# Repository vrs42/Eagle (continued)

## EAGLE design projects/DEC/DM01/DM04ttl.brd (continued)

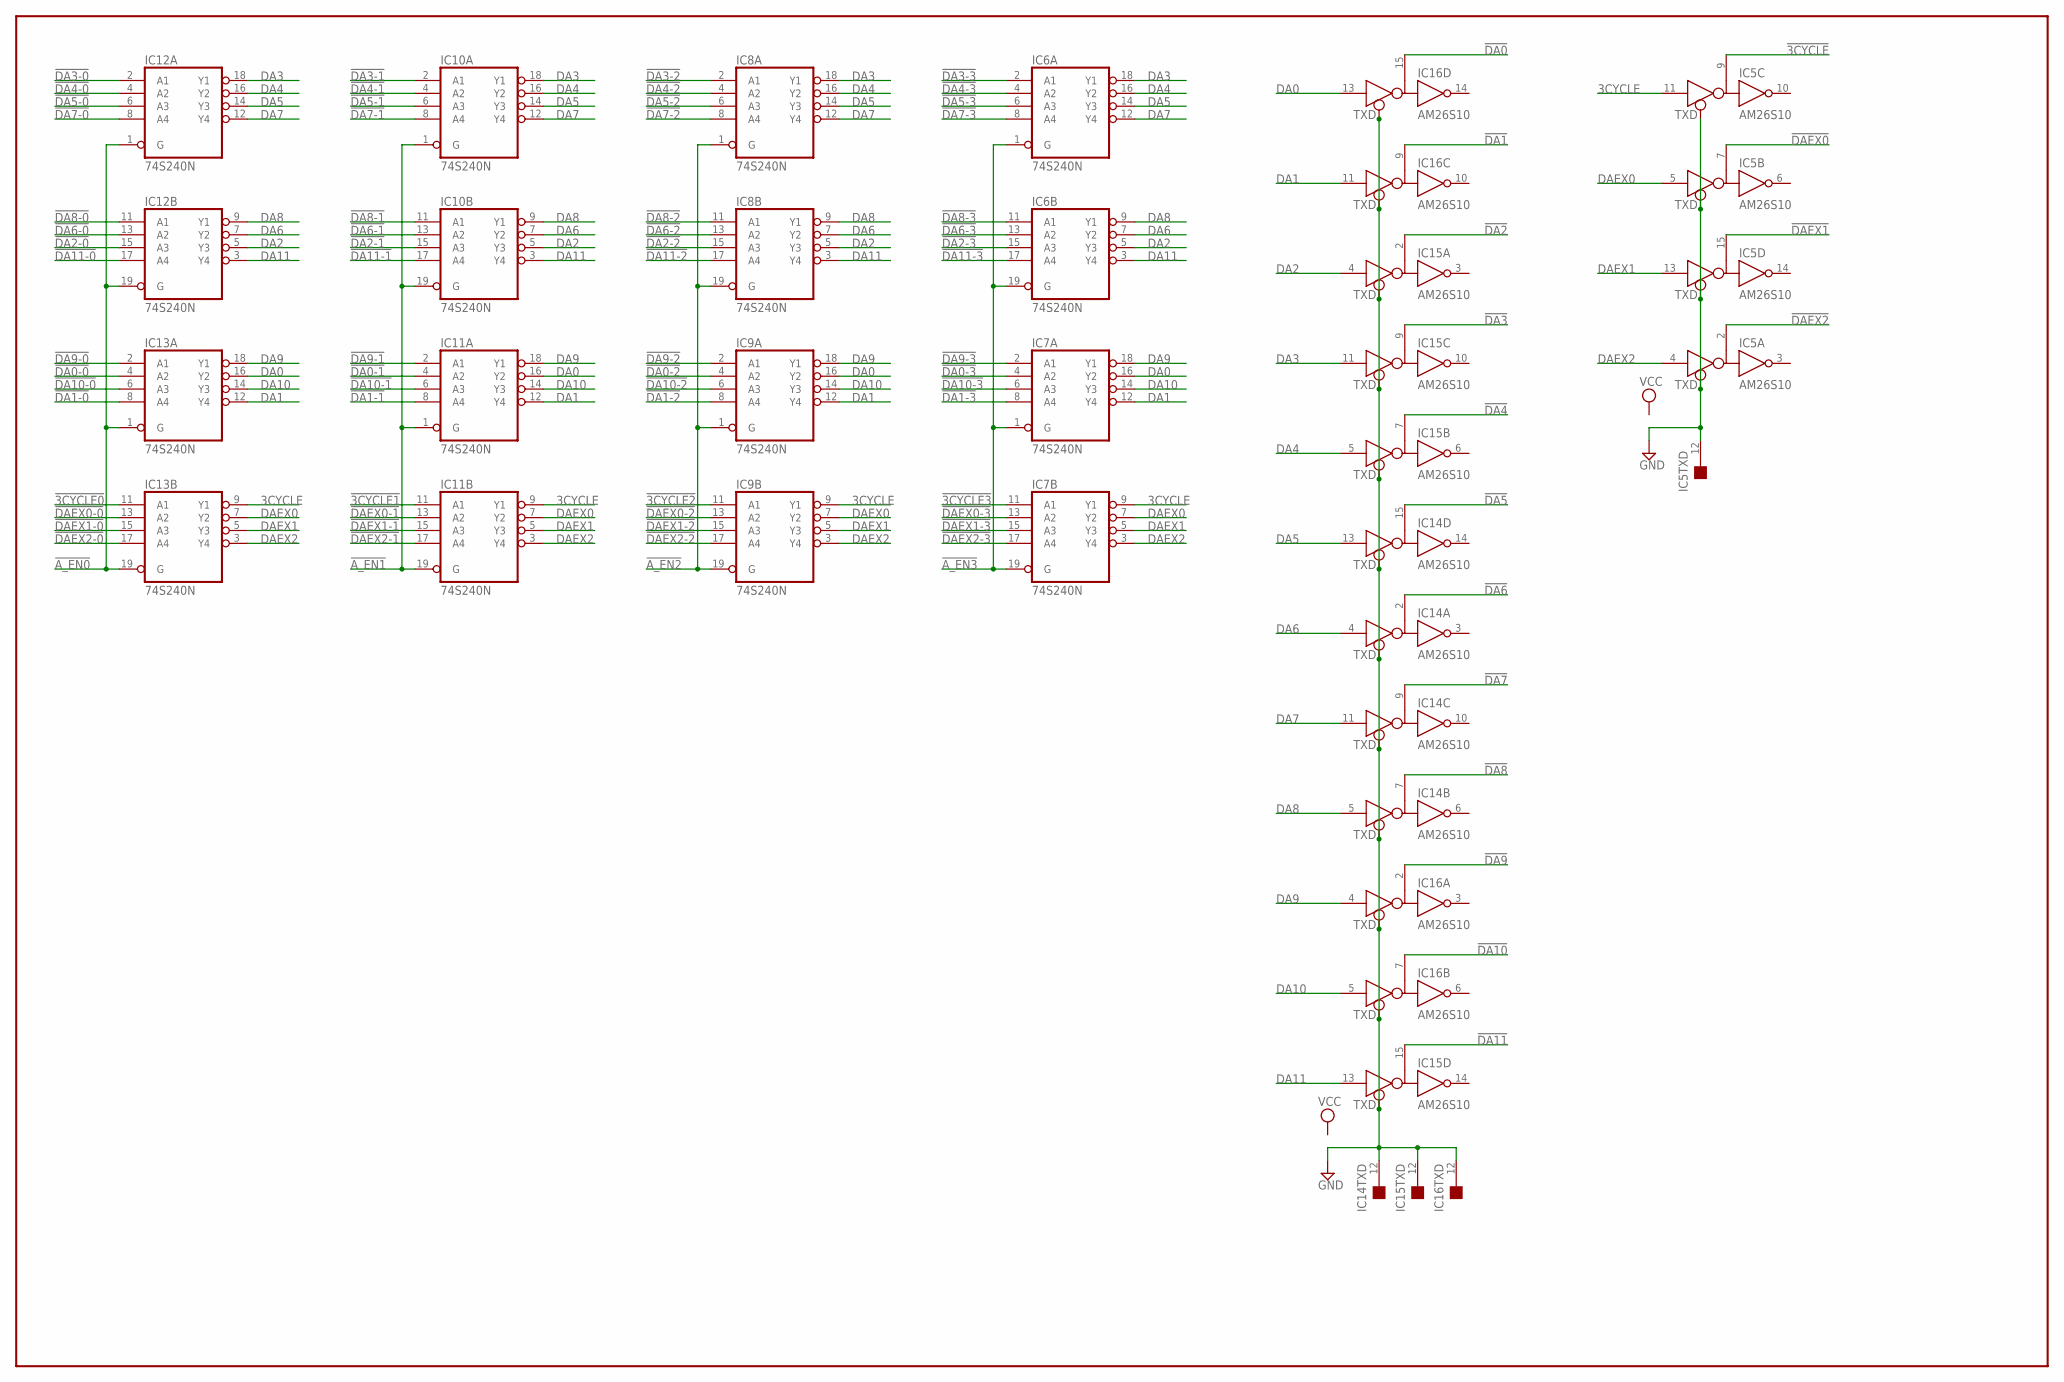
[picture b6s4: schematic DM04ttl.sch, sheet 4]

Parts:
IC5, IC14, IC15, IC16: AM26S10; DIL16
IC6, IC7, IC8, IC9, IC10, IC11, IC12, IC13: 74S240N; DIL20

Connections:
3CYCLE: IC5.11 (D), IC7.9 (Y1), IC9.9 (Y1), IC11.9 (Y1), IC13.9 (Y1)
!3CYCLE: IC5.9 (B); also elsewhere on the board
!3CYCLE0: IC13.11 (A1); also elsewhere on the board
!3CYCLE1: IC11.11 (A1); also elsewhere on the board
!3CYCLE2: IC9.11 (A1); also elsewhere on the board
!3CYCLE3: IC7.11 (A1); also elsewhere on the board
!A_EN0: IC12.1 (G), IC12.19 (G), IC13.1 (G), IC13.19 (G); also elsewhere on the board
!A_EN1: IC10.1 (G), IC10.19 (G), IC11.1 (G), IC11.19 (G); also elsewhere on the board
!A_EN2: IC8.1 (G), IC8.19 (G), IC9.1 (G), IC9.19 (G); also elsewhere on the board
!A_EN3: IC6.1 (G), IC6.19 (G), IC7.1 (G), IC7.19 (G); also elsewhere on the board
!DA0: IC16.15 (B); also elsewhere on the board
!DA0-0: IC13.4 (A2); also elsewhere on the board
!DA0-1: IC11.4 (A2); also elsewhere on the board
!DA0-2: IC9.4 (A2); also elsewhere on the board
!DA0-3: IC7.4 (A2); also elsewhere on the board
!DA1: IC16.9 (B); also elsewhere on the board
!DA1-0: IC13.8 (A4); also elsewhere on the board
!DA1-1: IC11.8 (A4); also elsewhere on the board
!DA1-2: IC9.8 (A4); also elsewhere on the board
!DA1-3: IC7.8 (A4); also elsewhere on the board
!DA2: IC15.2 (B); also elsewhere on the board
!DA2-0: IC12.15 (A3); also elsewhere on the board
!DA2-1: IC10.15 (A3); also elsewhere on the board
!DA2-2: IC8.15 (A3); also elsewhere on the board
!DA2-3: IC6.15 (A3); also elsewhere on the board
!DA3: IC15.9 (B); also elsewhere on the board
!DA3-0: IC12.2 (A1); also elsewhere on the board
!DA3-1: IC10.2 (A1); also elsewhere on the board
!DA3-2: IC8.2 (A1); also elsewhere on the board
!DA3-3: IC6.2 (A1); also elsewhere on the board
!DA4: IC15.7 (B); also elsewhere on the board
!DA4-0: IC12.4 (A2); also elsewhere on the board
!DA4-1: IC10.4 (A2); also elsewhere on the board
!DA4-2: IC8.4 (A2); also elsewhere on the board
!DA4-3: IC6.4 (A2); also elsewhere on the board
!DA5: IC14.15 (B); also elsewhere on the board
!DA5-0: IC12.6 (A3); also elsewhere on the board
!DA5-1: IC10.6 (A3); also elsewhere on the board
!DA5-2: IC8.6 (A3); also elsewhere on the board
!DA5-3: IC6.6 (A3); also elsewhere on the board
!DA6: IC14.2 (B); also elsewhere on the board
!DA6-0: IC12.13 (A2); also elsewhere on the board
!DA6-1: IC10.13 (A2); also elsewhere on the board
!DA6-2: IC8.13 (A2); also elsewhere on the board
!DA6-3: IC6.13 (A2); also elsewhere on the board
!DA7: IC14.9 (B); also elsewhere on the board
!DA7-0: IC12.8 (A4); also elsewhere on the board
!DA7-1: IC10.8 (A4); also elsewhere on the board
!DA7-2: IC8.8 (A4); also elsewhere on the board
!DA7-3: IC6.8 (A4); also elsewhere on the board
!DA8: IC14.7 (B); also elsewhere on the board
!DA8-0: IC12.11 (A1); also elsewhere on the board
!DA8-1: IC10.11 (A1); also elsewhere on the board
!DA8-2: IC8.11 (A1); also elsewhere on the board
!DA8-3: IC6.11 (A1); also elsewhere on the board
!DA9: IC16.2 (B); also elsewhere on the board
!DA9-0: IC13.2 (A1); also elsewhere on the board
!DA9-1: IC11.2 (A1); also elsewhere on the board
!DA9-2: IC9.2 (A1); also elsewhere on the board
!DA9-3: IC7.2 (A1); also elsewhere on the board
!DA10: IC16.7 (B); also elsewhere on the board
!DA10-0: IC13.6 (A3); also elsewhere on the board
!DA10-1: IC11.6 (A3); also elsewhere on the board
!DA10-2: IC9.6 (A3); also elsewhere on the board
!DA10-3: IC7.6 (A3); also elsewhere on the board
!DA11: IC15.15 (B); also elsewhere on the board
!DA11-0: IC12.17 (A4); also elsewhere on the board
!DA11-1: IC10.17 (A4); also elsewhere on the board
!DA11-2: IC8.17 (A4); also elsewhere on the board
!DA11-3: IC6.17 (A4); also elsewhere on the board
!DAEX0: IC5.7 (B); also elsewhere on the board
!DAEX0-0: IC13.13 (A2); also elsewhere on the board
!DAEX0-1: IC11.13 (A2); also elsewhere on the board
!DAEX0-2: IC9.13 (A2); also elsewhere on the board
!DAEX0-3: IC7.13 (A2); also elsewhere on the board
!DAEX1: IC5.15 (B); also elsewhere on the board
!DAEX1-0: IC13.15 (A3); also elsewhere on the board
!DAEX1-1: IC11.15 (A3); also elsewhere on the board
!DAEX1-2: IC9.15 (A3); also elsewhere on the board
!DAEX1-3: IC7.15 (A3); also elsewhere on the board
!DAEX2: IC5.2 (B); also elsewhere on the board
!DAEX2-0: IC13.17 (A4); also elsewhere on the board
!DAEX2-1: IC11.17 (A4); also elsewhere on the board
!DAEX2-2: IC9.17 (A4); also elsewhere on the board
!DAEX2-3: IC7.17 (A4); also elsewhere on the board
DA0: IC7.16 (Y2), IC9.16 (Y2), IC11.16 (Y2), IC13.16 (Y2), IC16.13 (D)
DA1: IC7.12 (Y4), IC9.12 (Y4), IC11.12 (Y4), IC13.12 (Y4), IC16.11 (D)
DA2: IC6.5 (Y3), IC8.5 (Y3), IC10.5 (Y3), IC12.5 (Y3), IC15.4 (D)
DA3: IC6.18 (Y1), IC8.18 (Y1), IC10.18 (Y1), IC12.18 (Y1), IC15.11 (D)
DA4: IC6.16 (Y2), IC8.16 (Y2), IC10.16 (Y2), IC12.16 (Y2), IC15.5 (D)
DA5: IC6.14 (Y3), IC8.14 (Y3), IC10.14 (Y3), IC12.14 (Y3), IC14.13 (D)
DA6: IC6.7 (Y2), IC8.7 (Y2), IC10.7 (Y2), IC12.7 (Y2), IC14.4 (D)
DA7: IC6.12 (Y4), IC8.12 (Y4), IC10.12 (Y4), IC12.12 (Y4), IC14.11 (D)
DA8: IC6.9 (Y1), IC8.9 (Y1), IC10.9 (Y1), IC12.9 (Y1), IC14.5 (D)
DA9: IC7.18 (Y1), IC9.18 (Y1), IC11.18 (Y1), IC13.18 (Y1), IC16.4 (D)
DA10: IC7.14 (Y3), IC9.14 (Y3), IC11.14 (Y3), IC13.14 (Y3), IC16.5 (D)
DA11: IC6.3 (Y4), IC8.3 (Y4), IC10.3 (Y4), IC12.3 (Y4), IC15.13 (D)
DAEX0: IC5.5 (D), IC7.7 (Y2), IC9.7 (Y2), IC11.7 (Y2), IC13.7 (Y2)
DAEX1: IC5.13 (D), IC7.5 (Y3), IC9.5 (Y3), IC11.5 (Y3), IC13.5 (Y3)
DAEX2: IC5.4 (D), IC7.3 (Y4), IC9.3 (Y4), IC11.3 (Y4), IC13.3 (Y4)
GND: IC5.1 (GND), IC5.8 (GND), IC5.12 (TXD), IC6.10 (GND), IC7.10 (GND), IC8.10 (GND), IC9.10 (GND), IC10.10 (GND), IC11.10 (GND), IC12.10 (GND), IC13.10 (GND), IC14.1 (GND), IC14.8 (GND), IC14.12 (TXD), IC15.1 (GND), IC15.8 (GND), IC15.12 (TXD), IC16.1 (GND), IC16.8 (GND), IC16.12 (TXD); also elsewhere on the board
VCC: IC5.16 (VCC), IC6.20 (VCC), IC7.20 (VCC), IC8.20 (VCC), IC9.20 (VCC), IC10.20 (VCC), IC11.20 (VCC), IC12.20 (VCC), IC13.20 (VCC), IC14.16 (VCC), IC15.16 (VCC), IC16.16 (VCC); also elsewhere on the board

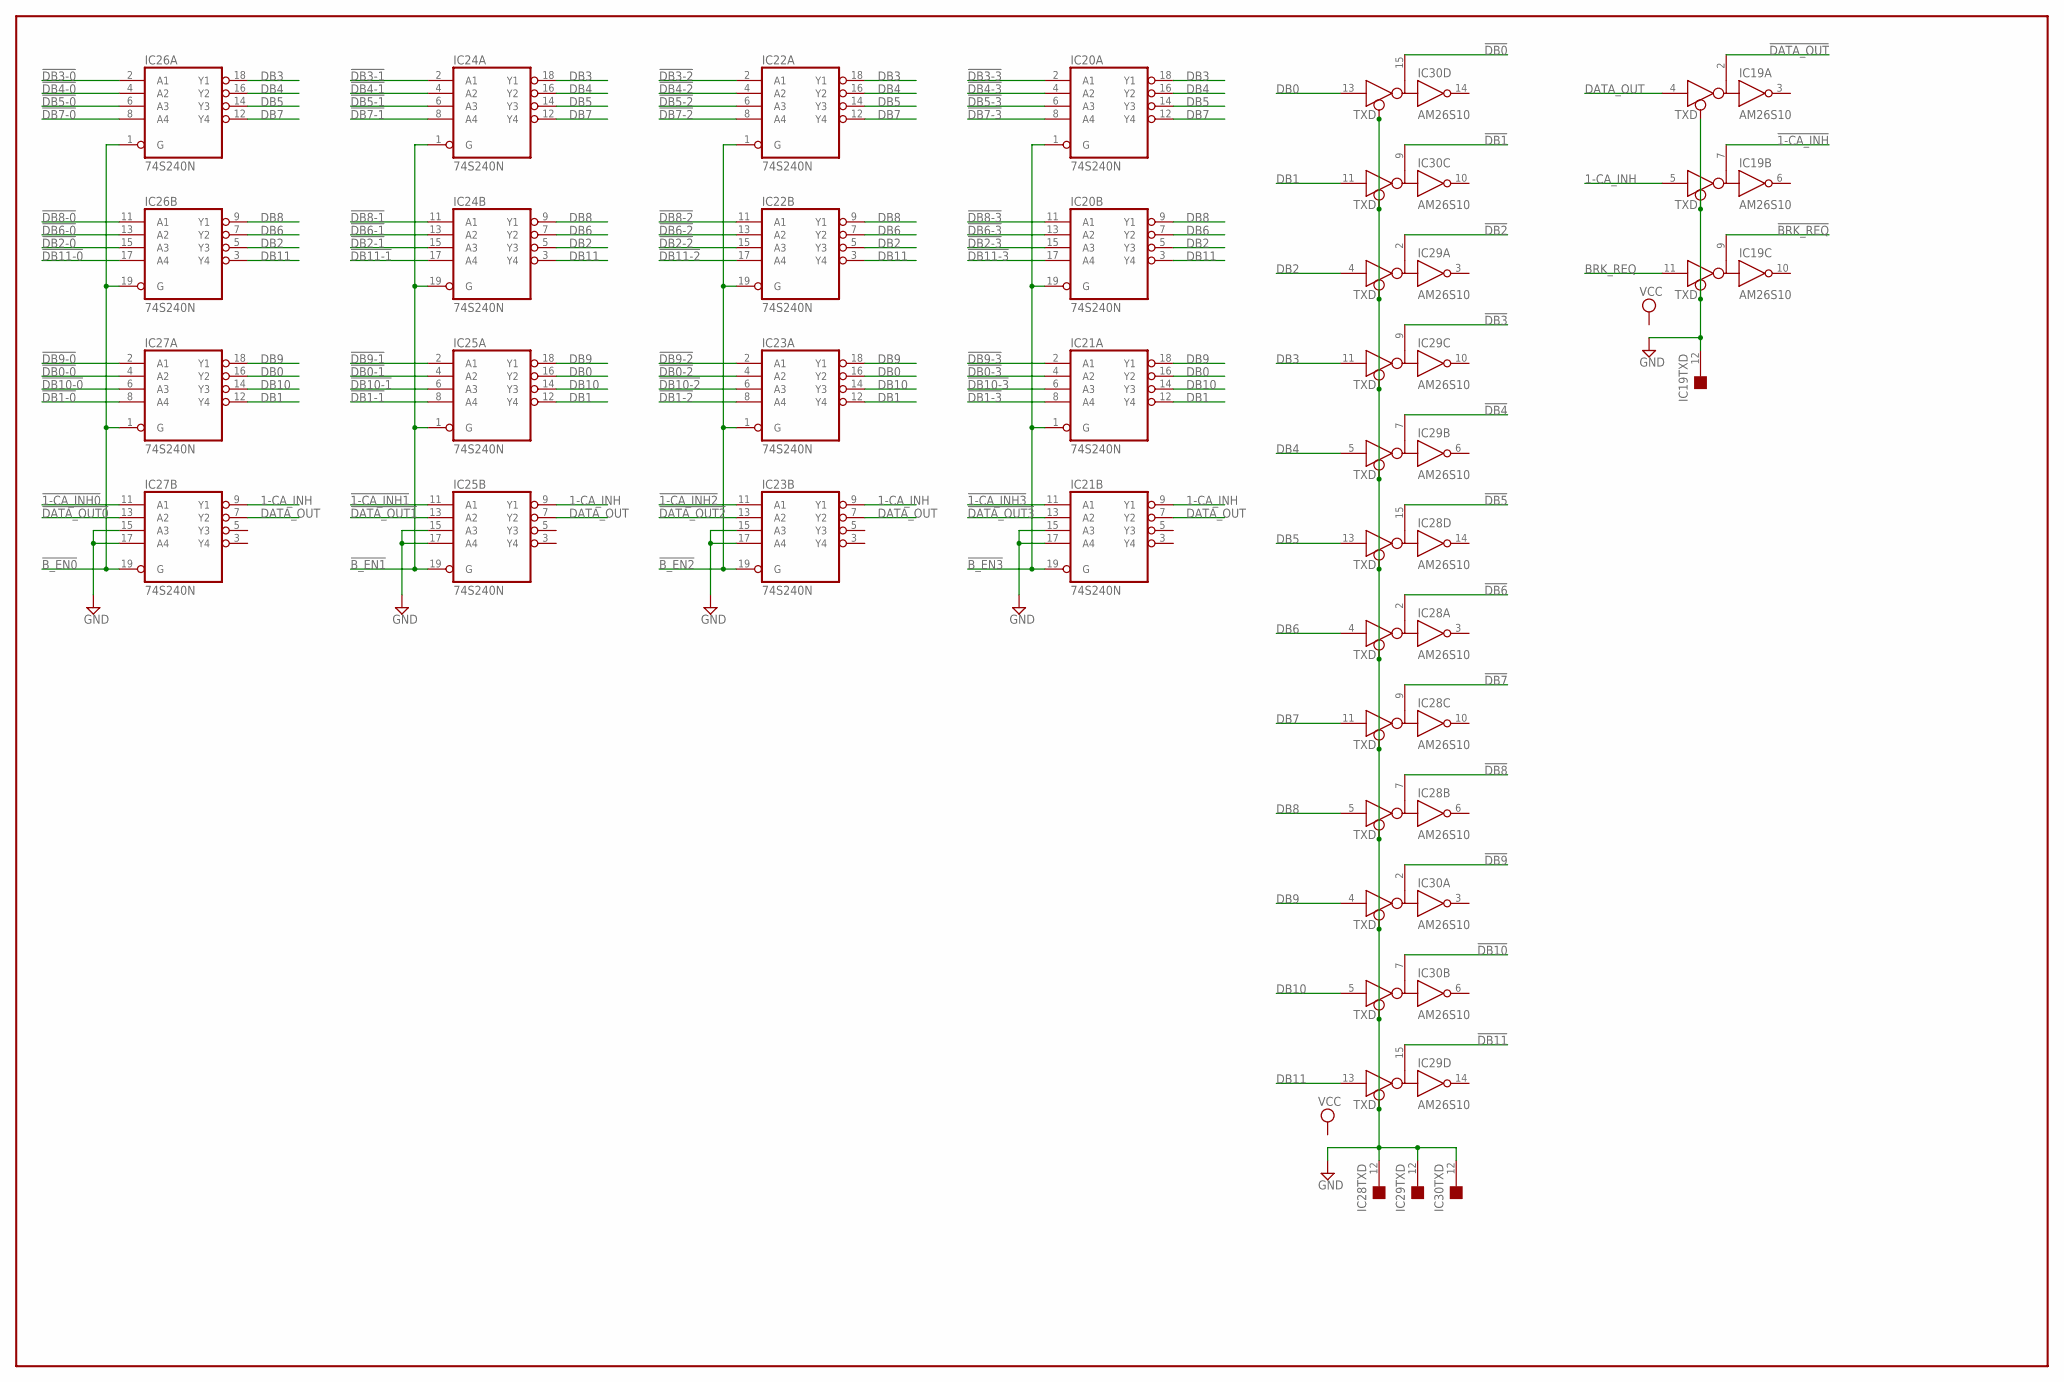
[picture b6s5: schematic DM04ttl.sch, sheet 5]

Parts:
IC19, IC28, IC29, IC30: AM26S10; DIL16
IC20, IC21, IC22, IC23, IC24, IC25, IC26, IC27: 74S240N; DIL20

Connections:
1-CA_INH: IC19.5 (D), IC21.9 (Y1), IC23.9 (Y1), IC25.9 (Y1), IC27.9 (Y1)
!1-CA_INH: IC19.7 (B); also elsewhere on the board
!1-CA_INH0: IC27.11 (A1); also elsewhere on the board
!1-CA_INH1: IC25.11 (A1); also elsewhere on the board
!1-CA_INH2: IC23.11 (A1); also elsewhere on the board
!1-CA_INH3: IC21.11 (A1); also elsewhere on the board
!BRK_REQ: IC19.9 (B); also elsewhere on the board
!B_EN0: IC26.1 (G), IC26.19 (G), IC27.1 (G), IC27.19 (G); also elsewhere on the board
!B_EN1: IC24.1 (G), IC24.19 (G), IC25.1 (G), IC25.19 (G); also elsewhere on the board
!B_EN2: IC22.1 (G), IC22.19 (G), IC23.1 (G), IC23.19 (G); also elsewhere on the board
!B_EN3: IC20.1 (G), IC20.19 (G), IC21.1 (G), IC21.19 (G); also elsewhere on the board
!DATA_OUT: IC19.2 (B); also elsewhere on the board
!DATA_OUT0: IC27.13 (A2); also elsewhere on the board
!DATA_OUT1: IC25.13 (A2); also elsewhere on the board
!DATA_OUT2: IC23.13 (A2); also elsewhere on the board
!DATA_OUT3: IC21.13 (A2); also elsewhere on the board
!DB0: IC30.15 (B); also elsewhere on the board
!DB0-0: IC27.4 (A2); also elsewhere on the board
!DB0-1: IC25.4 (A2); also elsewhere on the board
!DB0-2: IC23.4 (A2); also elsewhere on the board
!DB0-3: IC21.4 (A2); also elsewhere on the board
!DB1: IC30.9 (B); also elsewhere on the board
!DB1-0: IC27.8 (A4); also elsewhere on the board
!DB1-1: IC25.8 (A4); also elsewhere on the board
!DB1-2: IC23.8 (A4); also elsewhere on the board
!DB1-3: IC21.8 (A4); also elsewhere on the board
!DB2: IC29.2 (B); also elsewhere on the board
!DB2-0: IC26.15 (A3); also elsewhere on the board
!DB2-1: IC24.15 (A3); also elsewhere on the board
!DB2-2: IC22.15 (A3); also elsewhere on the board
!DB2-3: IC20.15 (A3); also elsewhere on the board
!DB3: IC29.9 (B); also elsewhere on the board
!DB3-0: IC26.2 (A1); also elsewhere on the board
!DB3-1: IC24.2 (A1); also elsewhere on the board
!DB3-2: IC22.2 (A1); also elsewhere on the board
!DB3-3: IC20.2 (A1); also elsewhere on the board
!DB4: IC29.7 (B); also elsewhere on the board
!DB4-0: IC26.4 (A2); also elsewhere on the board
!DB4-1: IC24.4 (A2); also elsewhere on the board
!DB4-2: IC22.4 (A2); also elsewhere on the board
!DB4-3: IC20.4 (A2); also elsewhere on the board
!DB5: IC28.15 (B); also elsewhere on the board
!DB5-0: IC26.6 (A3); also elsewhere on the board
!DB5-1: IC24.6 (A3); also elsewhere on the board
!DB5-2: IC22.6 (A3); also elsewhere on the board
!DB5-3: IC20.6 (A3); also elsewhere on the board
!DB6: IC28.2 (B); also elsewhere on the board
!DB6-0: IC26.13 (A2); also elsewhere on the board
!DB6-1: IC24.13 (A2); also elsewhere on the board
!DB6-2: IC22.13 (A2); also elsewhere on the board
!DB6-3: IC20.13 (A2); also elsewhere on the board
!DB7: IC28.9 (B); also elsewhere on the board
!DB7-0: IC26.8 (A4); also elsewhere on the board
!DB7-1: IC24.8 (A4); also elsewhere on the board
!DB7-2: IC22.8 (A4); also elsewhere on the board
!DB7-3: IC20.8 (A4); also elsewhere on the board
!DB8: IC28.7 (B); also elsewhere on the board
!DB8-0: IC26.11 (A1); also elsewhere on the board
!DB8-1: IC24.11 (A1); also elsewhere on the board
!DB8-2: IC22.11 (A1); also elsewhere on the board
!DB8-3: IC20.11 (A1); also elsewhere on the board
!DB9: IC30.2 (B); also elsewhere on the board
!DB9-0: IC27.2 (A1); also elsewhere on the board
!DB9-1: IC25.2 (A1); also elsewhere on the board
!DB9-2: IC23.2 (A1); also elsewhere on the board
!DB9-3: IC21.2 (A1); also elsewhere on the board
!DB10: IC30.7 (B); also elsewhere on the board
!DB10-0: IC27.6 (A3); also elsewhere on the board
!DB10-1: IC25.6 (A3); also elsewhere on the board
!DB10-2: IC23.6 (A3); also elsewhere on the board
!DB10-3: IC21.6 (A3); also elsewhere on the board
!DB11: IC29.15 (B); also elsewhere on the board
!DB11-0: IC26.17 (A4); also elsewhere on the board
!DB11-1: IC24.17 (A4); also elsewhere on the board
!DB11-2: IC22.17 (A4); also elsewhere on the board
!DB11-3: IC20.17 (A4); also elsewhere on the board
BRK_REQ: IC19.11 (D); also elsewhere on the board
DATA_OUT: IC19.4 (D), IC21.7 (Y2), IC23.7 (Y2), IC25.7 (Y2), IC27.7 (Y2)
DB0: IC21.16 (Y2), IC23.16 (Y2), IC25.16 (Y2), IC27.16 (Y2), IC30.13 (D)
DB1: IC21.12 (Y4), IC23.12 (Y4), IC25.12 (Y4), IC27.12 (Y4), IC30.11 (D)
DB2: IC20.5 (Y3), IC22.5 (Y3), IC24.5 (Y3), IC26.5 (Y3), IC29.4 (D)
DB3: IC20.18 (Y1), IC22.18 (Y1), IC24.18 (Y1), IC26.18 (Y1), IC29.11 (D)
DB4: IC20.16 (Y2), IC22.16 (Y2), IC24.16 (Y2), IC26.16 (Y2), IC29.5 (D)
DB5: IC20.14 (Y3), IC22.14 (Y3), IC24.14 (Y3), IC26.14 (Y3), IC28.13 (D)
DB6: IC20.7 (Y2), IC22.7 (Y2), IC24.7 (Y2), IC26.7 (Y2), IC28.4 (D)
DB7: IC20.12 (Y4), IC22.12 (Y4), IC24.12 (Y4), IC26.12 (Y4), IC28.11 (D)
DB8: IC20.9 (Y1), IC22.9 (Y1), IC24.9 (Y1), IC26.9 (Y1), IC28.5 (D)
DB9: IC21.18 (Y1), IC23.18 (Y1), IC25.18 (Y1), IC27.18 (Y1), IC30.4 (D)
DB10: IC21.14 (Y3), IC23.14 (Y3), IC25.14 (Y3), IC27.14 (Y3), IC30.5 (D)
DB11: IC20.3 (Y4), IC22.3 (Y4), IC24.3 (Y4), IC26.3 (Y4), IC29.13 (D)
GND: IC19.1 (GND), IC19.8 (GND), IC19.12 (TXD), IC20.10 (GND), IC21.10 (GND), IC21.15 (A3), IC21.17 (A4), IC22.10 (GND), IC23.10 (GND), IC23.15 (A3), IC23.17 (A4), IC24.10 (GND), IC25.10 (GND), IC25.15 (A3), IC25.17 (A4), IC26.10 (GND), IC27.10 (GND), IC27.15 (A3), IC27.17 (A4), IC28.1 (GND), IC28.8 (GND), IC28.12 (TXD), IC29.1 (GND), IC29.8 (GND), IC29.12 (TXD), IC30.1 (GND), IC30.8 (GND), IC30.12 (TXD); also elsewhere on the board
VCC: IC19.16 (VCC), IC20.20 (VCC), IC21.20 (VCC), IC22.20 (VCC), IC23.20 (VCC), IC24.20 (VCC), IC25.20 (VCC), IC26.20 (VCC), IC27.20 (VCC), IC28.16 (VCC), IC29.16 (VCC), IC30.16 (VCC); also elsewhere on the board

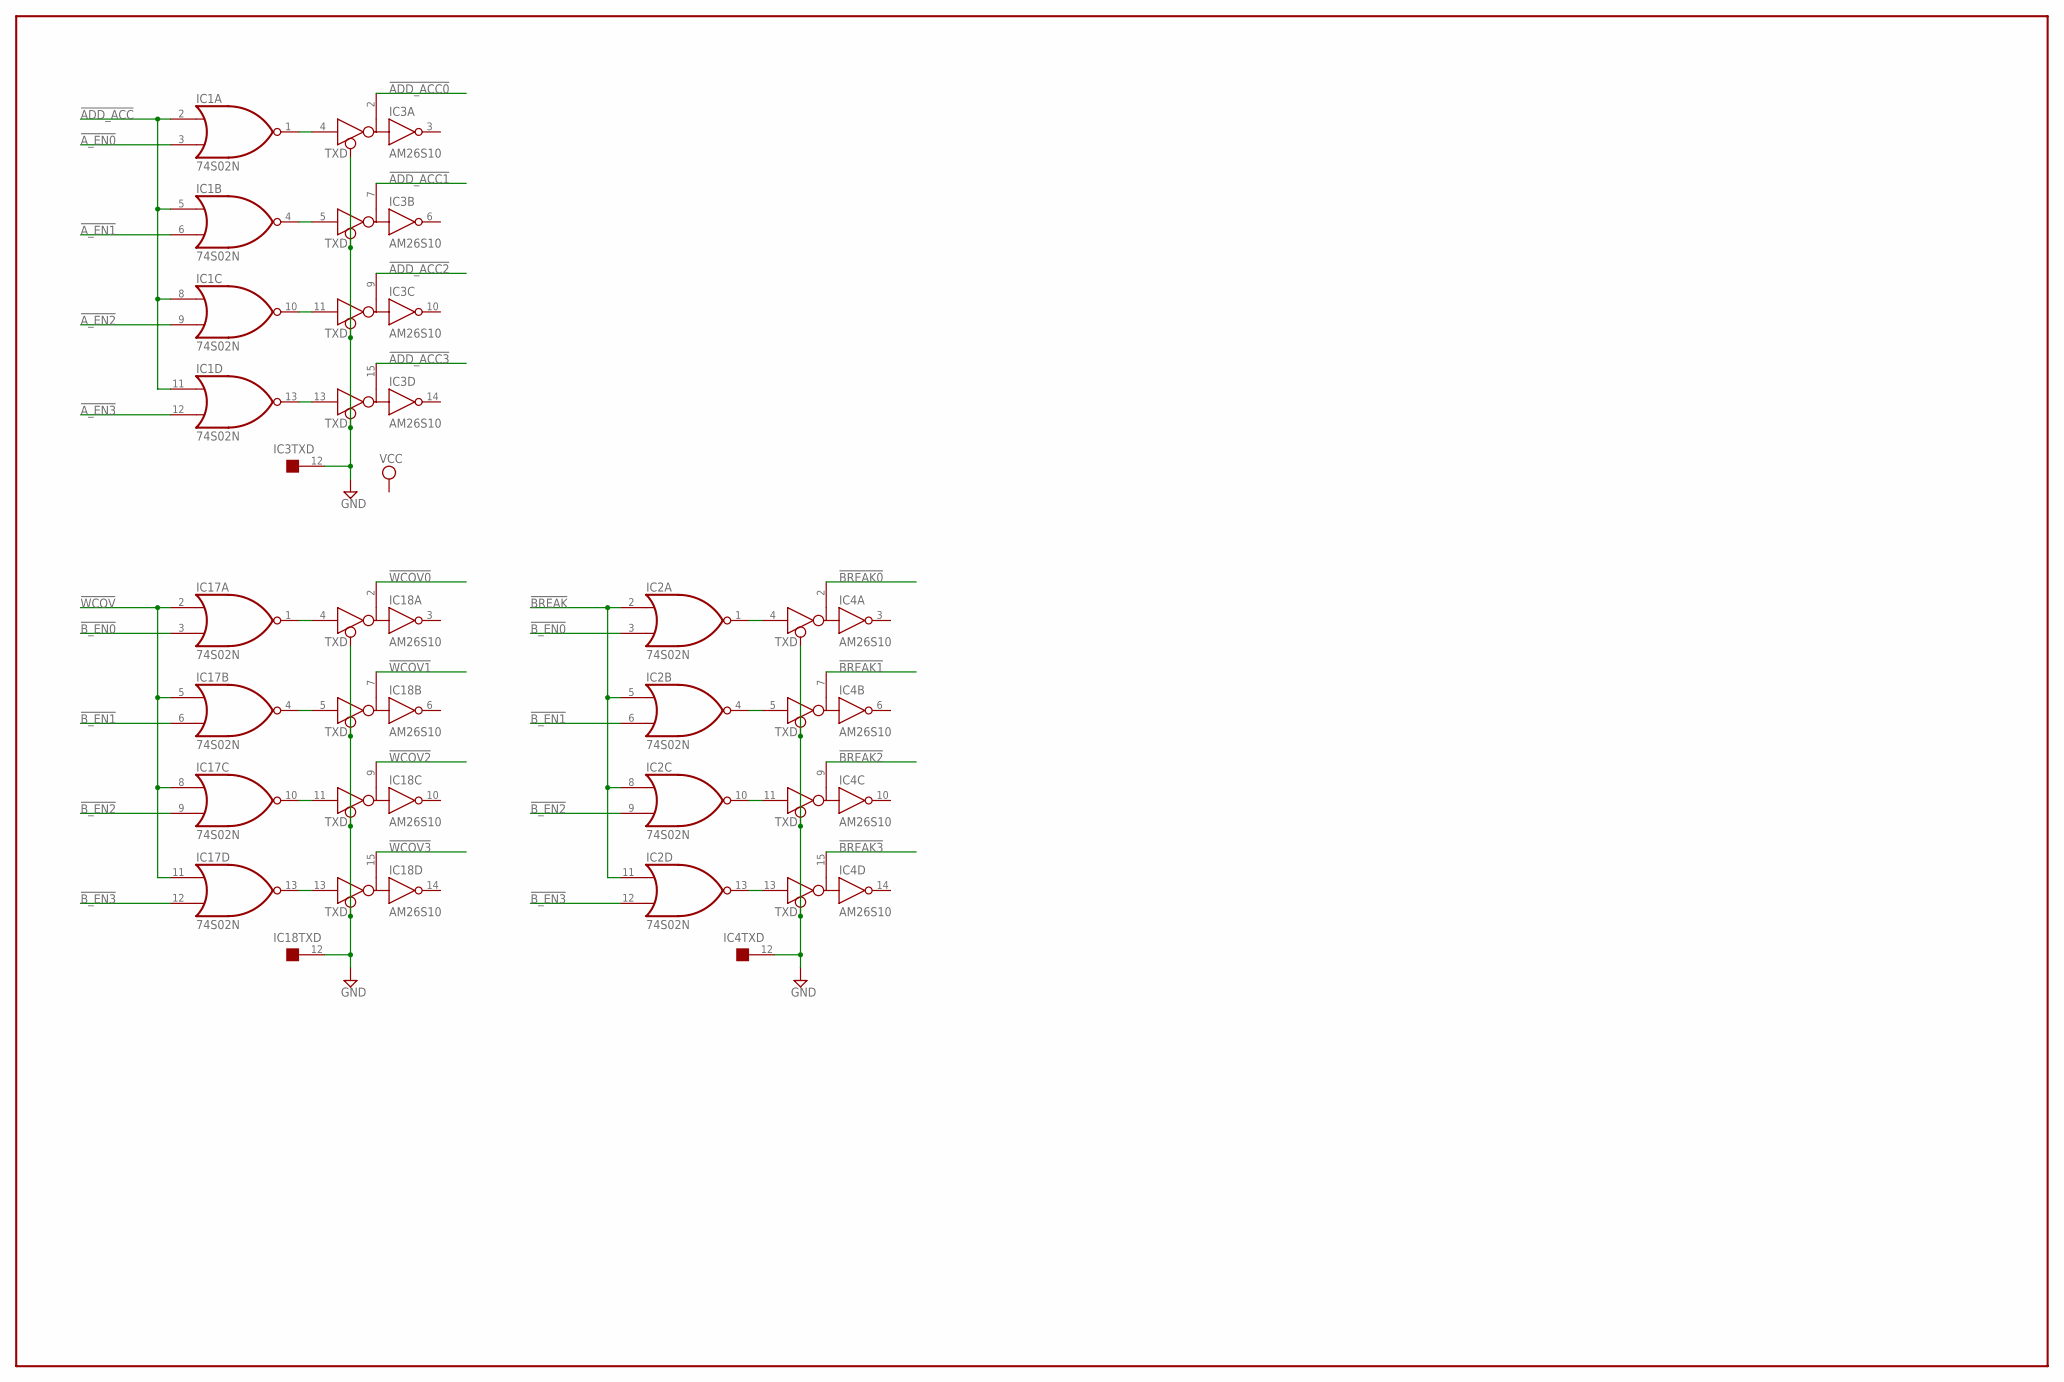
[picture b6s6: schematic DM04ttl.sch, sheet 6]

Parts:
IC1, IC2, IC17: 74S02N; DIL14
IC3, IC4, IC18: AM26S10; DIL16

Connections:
!ADD_ACC: IC1.2 (I0), IC1.5 (I0), IC1.8 (I0), IC1.11 (I0); also elsewhere on the board
!ADD_ACC0: IC3.2 (B); also elsewhere on the board
!ADD_ACC1: IC3.7 (B); also elsewhere on the board
!ADD_ACC2: IC3.9 (B); also elsewhere on the board
!ADD_ACC3: IC3.15 (B); also elsewhere on the board
!A_EN0: IC1.3 (I1); also elsewhere on the board
!A_EN1: IC1.6 (I1); also elsewhere on the board
!A_EN2: IC1.9 (I1); also elsewhere on the board
!A_EN3: IC1.12 (I1); also elsewhere on the board
!BREAK: IC2.2 (I0), IC2.5 (I0), IC2.8 (I0), IC2.11 (I0); also elsewhere on the board
!BREAK0: IC4.2 (B); also elsewhere on the board
!BREAK1: IC4.7 (B); also elsewhere on the board
!BREAK2: IC4.9 (B); also elsewhere on the board
!BREAK3: IC4.15 (B); also elsewhere on the board
!B_EN0: IC2.3 (I1), IC17.3 (I1); also elsewhere on the board
!B_EN1: IC2.6 (I1), IC17.6 (I1); also elsewhere on the board
!B_EN2: IC2.9 (I1), IC17.9 (I1); also elsewhere on the board
!B_EN3: IC2.12 (I1), IC17.12 (I1); also elsewhere on the board
!WCOV: IC17.2 (I0), IC17.5 (I0), IC17.8 (I0), IC17.11 (I0); also elsewhere on the board
!WCOV0: IC18.2 (B); also elsewhere on the board
!WCOV1: IC18.7 (B); also elsewhere on the board
!WCOV2: IC18.9 (B); also elsewhere on the board
!WCOV3: IC18.15 (B); also elsewhere on the board
GND: IC1.7 (GND), IC2.7 (GND), IC3.1 (GND), IC3.8 (GND), IC3.12 (TXD), IC4.1 (GND), IC4.8 (GND), IC4.12 (TXD), IC17.7 (GND), IC18.1 (GND), IC18.8 (GND), IC18.12 (TXD); also elsewhere on the board
unnamed: IC17.1 (O), IC18.4 (D)
unnamed: IC17.10 (O), IC18.11 (D)
unnamed: IC17.4 (O), IC18.5 (D)
unnamed: IC17.13 (O), IC18.13 (D)
unnamed: IC2.1 (O), IC4.4 (D)
unnamed: IC2.10 (O), IC4.11 (D)
unnamed: IC2.4 (O), IC4.5 (D)
unnamed: IC2.13 (O), IC4.13 (D)
unnamed: IC1.1 (O), IC3.4 (D)
unnamed: IC1.10 (O), IC3.11 (D)
unnamed: IC1.4 (O), IC3.5 (D)
unnamed: IC1.13 (O), IC3.13 (D)
VCC: IC1.14 (VCC), IC2.14 (VCC), IC3.16 (VCC), IC4.16 (VCC), IC17.14 (VCC), IC18.16 (VCC); also elsewhere on the board

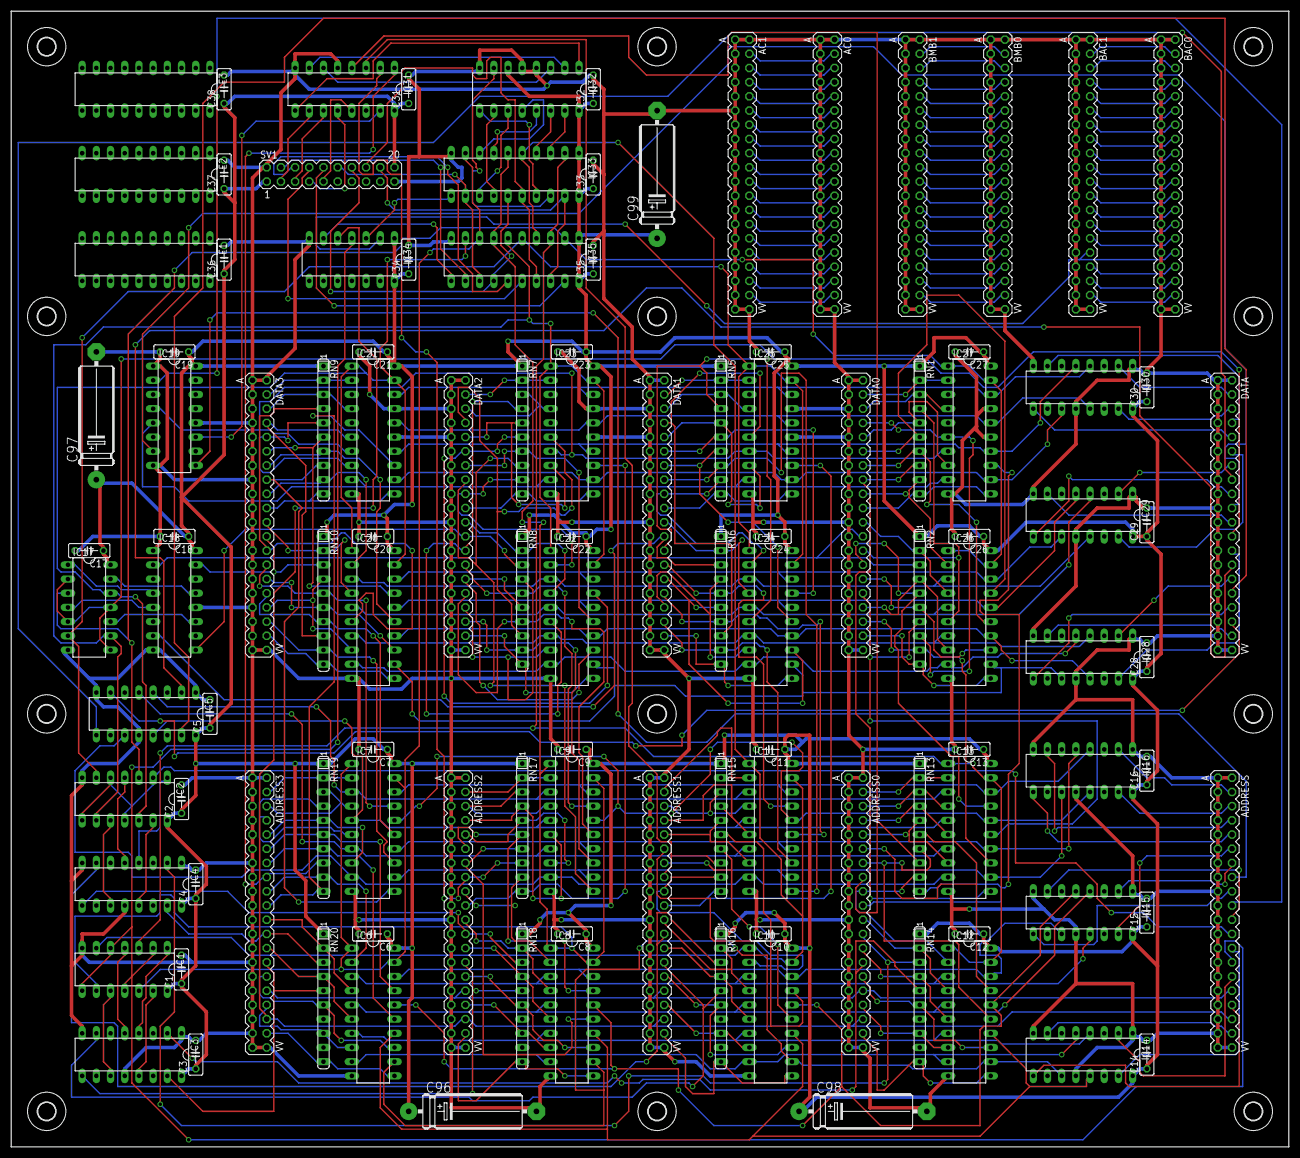
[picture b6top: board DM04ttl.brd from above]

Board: 2 copper layers, 228.6 x 203.2 mm, 125 parts (0 on the bottom side), 304 nets.

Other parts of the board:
U$1, U$2, U$3, U$4, U$5, U$6, U$7, U$8, U$9, U$10, U$11, U$12: 3,2
